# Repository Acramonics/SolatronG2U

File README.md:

G2U (SMD)
=========

Andrew Martin, acramonics, 2026
-------------------------------

`G2U` is a PCB for a GPIB to USB adapter using an Arduino Nano 3.
This is an SMD version to reduce size.

GPIB is a vendor-neutral interface for controlling equipment and
logging data. While rather outdated, and largely replaced by USB and
Ethernet, some equipment still uses it and there are many second hand
devices (such as multimeters) that use it including the well-regarded
Solartron 7150+.

A video on GPIB (also known as IEEE-488) is on
[YouTube](https://www.youtube.com/watch?v=EEtETGfL_VE) and details are
on [Wikipedia](https://en.wikipedia.org/wiki/GPIB).

The original circuit and software was by Rudolf Reuter and modified by
@TheHWCave. Rudolf's blog, where this was described, doesn't seem to
be available any more (as of March 2026), but @TheHWCave provides a
detailed description of the circuit on
[YouTube](https://www.youtube.com/watch?v=RaLirRvSngk) (see the
screenshots in the `SourceImages` directory).  He builds it on
stripboard and uses an Arduino breakout board, so I decided to create
a PCB instead.

There is another page with a [discussion of creating a GPIB/USB
interface](https://egirland.blogspot.com/2014/03/arduino-uno-as-usb-to-gpib-controller.html),
but note that this uses different pin assignments and different
software.

@TheHWCave was unable to obtain a PCB-mounted Centronics-style
(*Series 57*) 24-pin connector. They are also known as SCSI connectors
(technically SCSI-I; later SCSI versions use other connectors), or
Centronics connectors, and occasionally as IEEE-488 connectors!

The right-angled (horizontal) version of these is now easily available
from AliExpress (at about £2.50 with free postage if you spend more
than £8.00), and I have used a PCB-mounted **male** connector that can
plug straight into the back of the hardware, so you don't need to
worry about cables.

Hardware
--------

### Series 57 Connector

My design places the *Series 57* connector on the back of the board
and the *Arduino Nano* on the front with 1206 SMD resistors on both
front and back. The board (in its case if desired) then lies flat
against the back of the meter with the USB Arduino connection to the
left hand side.

The design uses the **straight vertical pinned** version of the
*Series 57* connector which is more difficult to find than the
right-angled version. You will find these described as 'pin type' or
'panel type'. The solder cup vertical version (also called 'line
type') are much easier to find, but these are **not** what you want!

*NorComp* seems to be the most common manufacturer and you want the
'111' series for straight connectors ('112' series is right-angle
while '211/212' are the female versions).  Specifically, the part
number you want for a straight connector is `111-024-113L001`.  At the
time of writing (May 2026), in the UK these are available from
[Mouser](https://www.mouser.co.uk/ProductDetail/NorComp/111-024-113L001?qs=IGgAdOvCTsTzuqCRtmjabw%3D%3D),
[Farnell](https://uk.farnell.com/norcomp/111-024-113l001/connector-scsi-plug-24-position/dp/2471322)
(to special order) and
[DigiKey](https://www.digikey.co.uk/en/products/detail/norcomp-inc/111-024-113L001/955147).

A much cheaper equivalent is available from AliExpress, but they are
hard to track down amongst all the right-angled and solder-cup
versions.  I found them on the [SKYWIN
Store](https://www.aliexpress.com/item/1005005636771892.html) (Store
no.:1102628842). Select 'Panel Type', 24P, Male.  You **must** ensure
you have the male connector! They are about £1.00 each plus £2.76
postage.

### Case

I designed this to fit in a nominal 83x54x30mm ABS plastic box
available from [Amazon](https://www.amazon.co.uk/dp/B0D44WNKD3). These
are the nominal external dimensions, the internal dimensions being
approximately 78x49x26mm. Each corner has a post for screwing on the
lid so the board has 7.5mm cutouts in each corner to accommodate
these.

Of course, you can use a larger case and fit the board at one end.
Alternatively, you could feed a USB cable and a 24pin *Series 57*
(Centronics) cable through holes in a larger case and just mount the
board anywhere in the case. This would also allow you to use one of
the easier-to-obtain right-angle (horizontal) *Series 57* connectors.
You need to use a male-to-female cable for the *Series 57*
connection.

As above, you **must use a male connector** - the pin connections
would be incorrect for a female connector - and this is why you would
need to male-to-female cable. If you really did want to use a female
*Series 57* connector with a male-to-male cable, then you would need
to wire the cable to cross over the pins.

Software
--------

@TheHWCave provides the code for the Arduino Nano 3 and a logger
script on [GitHub](https://github.com/TheHWcave/GPIB-to-USB).

He provides an [update
video](https://www.youtube.com/watch?v=DAS1KVU_FaA) which explains how
to address a problem with the Arduino losing its software when the USB
us disconnected, but the GPIB connection is still present. The GPIB
seems to provide some partial power to the Arduino and he provides
instructions on setting a brown-out fuse in software.

I provide a summary of all the necessary information on this page.

The PCB
-------

You can download a ZIP file of the Gerber files.  If you wish to
tinker with the KiCad files, as is often the case with my PCBs, you
will require my `ACRM_KiCad_Libs` to provide the footprint for the
24-pin male Centronics-style connector. You will need a version from
May 2026 or later.

Bill of Materials
-----------------

- Arduino ATmega Nano 3.x with USB (ideally USB-C) [1 off]
- 6K2 1206 SMD resistors (R1-R16) [16 off]
- 120R 1206 SMD resistors (R17-R32) [16 off]
- Centronics-style 24P 'Series 57' male connector (see above) [1 off]
- 83x54x30mm ABS plastic box (see above) [1 off]

The Centronics-style connector projects from the rear of the board so
will need a suitable cutout in the back of the case. The USB connector
is at the edge of the board so the case will also need a cutout at the
side.

Ardunio to GPIB connections
---------------------------

This table is expanded from a table shown in @TheHWCave's video (see
the screenshot in the `SourceImages` directory) and shows which
connections from the Arduino go to which pins on the GPIB. The Arduino
pins are shown with the pin number (from 1-30) and the position on the
left (L) or right (R) column of pins - both counting from the top.

| Arduino Line | Arduino Pin |     | GPIB Pin | Function | ATmega328P          |
|--------------|-------------|-----|----------|----------|---------------------|
| A0           | 19/R12      | --- | 1        | DIO1     | (PC0/ADC0)          |
| A1           | 20/R11      | --- | 2        | DIO2     | (CP1/ADC1)          |
| A2           | 21/R10      | --- | 3        | DIO3     | (PC2/ADC2)          |
| A3           | 22/R9       | --- | 4        | DIO4     | (PC3/ADC3)          |
| A4           | 23/R8       | --- | 13       | DIO5     | (PC4/ADC4)          |
| A5           | 24/R7       | --- | 14       | DIO6     | (PC5/ADC5)          |
| D10          | 13/L13      | --- | 15       | DIO7     | (PB2)               |
| D11          | 14/L14      | --- | 16       | DIO8     | (PB3(MOSI))         |
| D8           | 11/L11      | --- | 5        | EIO      | (PB0)               |
| D7           | 10/L10      | --- | 6        | DAV      | (PD7)               |
| D6           |  9/L9       | --- | 7        | NRFD     | (PD6)               |
| D5           |  8/L8       | --- | 8        | NDAC     | (PD5)               |
| D4           |  7/L7       | --- | 9        | IFC      | (PD4)               |
| D3           |  6/L6       | --- | 10       | SRQ      | (PD3)               |
| D2           |  5/L5       | --- | 11       | ATN      | (PD2)               |
| D9           | 12/L12      | --- | 17       | REN      | (PB1)               |
| GND          |  4/L4       | --- | 12,18-24 | GND      |                     |
| GND          | 29/R2       | --- | 12,18-24 | GND      |                     |
| +5V          | 27/R4       | +5V |          |          |                     |
| D1/TX1       |  1/L1       | NC  |          |          |                     |
| RX0          |  2/L2       | NC  |          |          |                     |
| RESET        |  3/L3       | NC  |          |          |                     |
| D12          | 15/L15      | NC  |          |          |                     |
| VIN          | 30/R1       | NC  |          |          |                     |
| RESET2       | 28/R3       | NC  |          |          |                     |
| A7           | 26/R5       | NC  |          |          |                     |
| A6           | 25/R6       | NC  |          |          |                     |
| AREF         | 18/R13      | NC  |          |          |                     |
| +3V3         | 17/R14      | NC  |          |          |                     |
| D13          | 16/R15      | NC  |          |          |                     |

Note that each GND pin in the GPIB connector is paired with one of the
data lines in a twisted pair. Pin 12 is connected to the cable shield.
See [GPIB on WikiPedia](https://en.wikipedia.org/wiki/GPIB). In this
application, this is rather irrelevant as everything is connected to a
common ground.

The Brown-Out Fuse
------------------

As described above, @TheHWCave provides an [update
video](https://www.youtube.com/watch?v=DAS1KVU_FaA) which explains how
to set the 'brown-out fuse' on the Arduino to prevent it losing its
software.

The 'extended fuse byte' has three bits that set the Brown-Out
Detector voltage level ('BODLEVEL'). When the voltage falls below
this, the chip is disabled.

|Extended Fuse Byte | Bit No | Default Value |
|-------------------|--------|---------------|
|-                  | 7      | 1             |
|-                  | 6      | 1             |
|-                  | 5      | 1             |
|-                  | 4      | 1             |
|-                  | 3      | 1             |
|BODLEVEL2          | 2      | 1 (unset)     |
|BODLEVEL1          | 1      | 1 (unset)     |
|BODLEVEL0          | 0      | 1 (unset)     |

The values for the BODLEVEL bits are as follows:

|BODLEVEL 2:0 Fuses | Hex (*)  | Min V    | Typ V    | Max V    | Units |
|-------------------|----------|----------|----------|----------|-------|
|111                | 0x07     | Off      | Off      | Off      |       |
|110                | 0x06     | 1.7      | 1.8      | 2.0      | V     |
|101                | 0x05     | 2.5      | 2.7      | 2.9      | V     |
|100                | 0x04     | 4.1      | 4.3      | 4.5      | V     |
|011                | 0x03     | Reserved | Reserved | Reserved |       |
|010                | 0x02     | Reserved | Reserved | Reserved |       |
|001                | 0x01     | Reserved | Reserved | Reserved |       |
|000                | 0x00     | Reserved | Reserved | Reserved |       |

(*) Since bits 3 to 7 are not used, these can all be set to zero and
the Hex values reflect that.

By default the fuse is set to #FF, the BODLEVEL bits are therefore set
to binary 111 which means the brown-out fuse is switched off.

@TheHWCave selects a BODLEVEL of 4.1V (minimal) so sets the
fuse to binary 100 (#04) for 4.1V cutoff.

Instructions on how to do this are provided below.

Software Installation
---------------------

You will need:

- A USB cable to connect your computer to your Arduino Nano
- An ICSP programmer with a 6-pin header adapter to connect to the
  Nano.  There are instructions online to use another Arduino for this
  purpose or you can buy a standalone programmer such as the USBASP
  programmers available from Amazon (amongst other places).

You will need the software available from
https://github.com/TheHWcave/GPIB-to-USB

Using this is explained in the video at
https://www.youtube.com/watch?v=RaLirRvSngk

### Step 1: The Arduino IDE

Install the Arduino IDE as described on the [Arduino Web
Site](https://support.arduino.cc/hc/en-us/articles/360019833020-Download-and-install-Arduino-IDE)

### Step 2: Configure the IDE for the Arduino Nano ATmega chip you are using [OPTIONAL]

Different Arduinos use different chips which have different signature
bytes and this needs to match the programmer:

Chip        | Byte 0x000 | Byte 0x001 | Byte 0x002
------------|------------|------------|------------
ATmega328   | 0x1E       | 0x95       | 0x14
ATmega328P  | 0x1E       | 0x95       | 0x0F
ATmega328PB | 0x1E       | 0x95       | 0x16

If the configuration doesn't match your chip then, for example, the
Arduino IDE may call AVRDude (used to set the fuse) expecting to find
an ATmega328P, but AVRDude finds an ATmega328PB and stops.

The configuration can be set in a configuration file or by manually
re-running the failed command, but correcting for the appropriate
chip. (See instructions below.)

If using Linux, the easest thing to do is create configuration file:
`~/.avrduderc` containing:

```
part parent "m328"
    id                  = "m328p";
    desc                = "ATmega328P";
    signature           = 0x1e 0x95 0x14;
    ocdrev              = 1;
;
```
setting the `id`, `desc` and `signature` as required depending on what
ATmega chip you have with signature bytes set as per the table above.

Alternatively you can allow AVRDude from the IDE to fail and then run
the fixed command manually as described below.

### Step 3: Setting the Brown-Out Fuse

*I will write a more detailed version when I have verified this on a
couple of Arduino Nano boards. This is largely in note form!*

As described above, you will need a second Arduino, or an ICSP
programmer spported by the Arduino IDE, to set the fuse. The IDE runs
the AVRDude software to perform the programming of the Brown-Out Fuse.

*To set the fuse from the Arduino IDE, proceed as follows --- to be written*

See:
- https://forum.arduino.cc/t/is-there-brown-out-detection-for-arduino-uno/124777/18
- https://electronics.stackexchange.com/questions/229189/atmega328p-how-is-brown-out-detection-supposed-to-work
- https://forum.arduino.cc/t/unable-to-set-fuses-on-atmega328p-using-avrdude-in-command-prompt-windows/1067499/5

Set the IDE to run in verbose mode so you can see what it is doing as
[described
here](https://support.arduino.cc/hc/en-us/articles/4407705216274-Use-verbose-output-in-the-Arduino-IDE)

If you have configured the IDE properly, then it should work with no
errors.  If you haven't then the AVRDude software will fail since the
chip's signature doesn't match what the software expected. The
workaround for this is described in @TheHWCave's video at
https://www.youtube.com/watch?v=DAS1KVU_FaA and summarized below.

If AVRDude fails, simply copy the failed command from the upload
window and run it from the command line instead, correcting the
errornous chip type. For example, assuming the Arduino IDE is
configured for an ATmega328P and your Nano has an ATmega328PM and
assuming that the IDE is installed in a directory pointed to by the
environment variable `$ARDUINO` (e.g. `$HOME/arduino-1.8.9`), you
might see the failed command to be:

```
$ARDUINO/hardware/tools/avr/bin/avrdude \
   -C$ARDUINO/hardware/tools/avr/etc/avrdude.conf \
   -v -patmega328p \
   -cusbasp -Pusb -e -Ulock:w:0x3F:m -Uefuse:w:0xF4:m \
   -Uhfuse:w:0xDA:m -Ulfuse:w:0xFF:m
```
and you would modify this to
```
$ARDUINO/hardware/tools/avr/bin/avrdude \
   -C$ARDUINO/hardware/tools/avr/etc/avrdude.conf \
   -v -patmega328pb \
   -cusbasp -Pusb -e -Ulock:w:0x3F:m -Uefuse:w:0xF4:m \
   -Uhfuse:w:0xDA:m -Ulfuse:w:0xFF:m
```
(note the change in the 3rd line) and run it from the command line

### Step 4: Restoring the bootloader

Setting the fuse erases the memory, so you then need to restore the bootloader.

Instructions on doing this from the IDE are [described here](https://support.arduino.cc/hc/en-us/articles/4841602539164-Burn-the-bootloader-on-UNO-Mega-and-classic-Nano-using-another-Arduino#ide)

Alternatively, you can do it from the command line using AVRDude:

```
~/arduino-1.8.9/hardware/tools/avr/bin/avrdude \
   -C~/arduino-1.8.9/hardware/tools/avr/etc/avrdude.conf \
   -v -patmega328pb \
   -cusbasp -Pusb -Uflash:w:./optiboot_atmega328.hex
```

This also allows the latest bootloader to be downloaded and installed.
See

- https://forum.arduino.cc/t/how-do-i-install-optiboot-on-the-newest-arduino-ide/345443
- https://github.com/Optiboot/optiboot

The latest, as of March 2026, is
https://github.com/Optiboot/optiboot/releases/download/v8.0/package_optiboot_optiboot-additional_index.json

### Step 5: Installing the Arduino software

You can then remove the in-circuit programmer and upload the
GPIB-to-USB software sketch in the normal way from the Arduino IDE
through the USB cable and with the newly installed boot loader.

*To be written.*

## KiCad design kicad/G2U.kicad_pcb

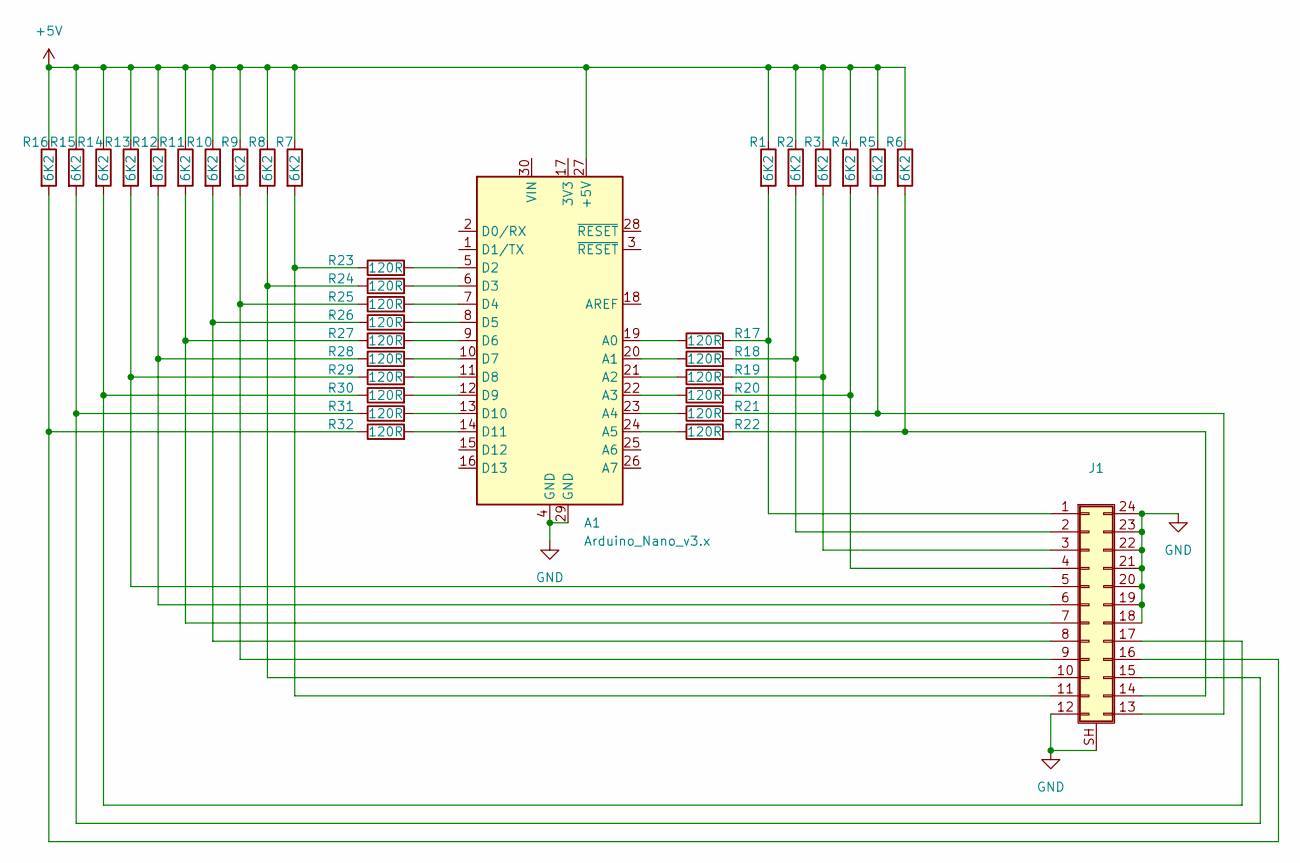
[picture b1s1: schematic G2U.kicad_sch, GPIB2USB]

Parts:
A1: Arduino_Nano_v3.x; Arduino_Nano
J1: Conn_02x12_Counter_Clockwise_Shielded; Connector_CentronicsMale-2x12_P2.16mm_P4.29_Vertical
R1, R2, R3, R4, R5, R6, R7, R8, R9, R10, R11, R12, R13, R14, R15, R16: 6K2; R_1206_3216Metric_Pad1.30x1.75mm_HandSolder
R17, R18, R19, R20, R21, R22, R23, R24, R25, R26, R27, R28, R29, R30, R31, R32: 120R; R_1206_3216Metric_Pad1.30x1.75mm_HandSolder

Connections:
+5V: A1.27 (+5V), R1.1, R2.1, R3.1, R4.1, R5.1, R6.1, R7.1, R8.1, R9.1, R10.1, R11.1, R12.1, R13.1, R14.1, R15.1, R16.1
GND: A1.4 (GND), A1.29 (GND), J1.12, J1.18, J1.19, J1.20, J1.21, J1.22, J1.23, J1.24, J1.SH (Shield)
unnamed: A1.19 (A0), R17.1
unnamed: A1.20 (A1), R18.1
unnamed: A1.21 (A2), R19.1
unnamed: A1.22 (A3), R20.1
unnamed: A1.23 (A4), R21.1
unnamed: A1.24 (A5), R22.1
unnamed: A1.5 (D2), R23.2
unnamed: A1.6 (D3), R24.2
unnamed: A1.7 (D4), R25.2
unnamed: A1.8 (D5), R26.2
unnamed: A1.9 (D6), R27.2
unnamed: A1.10 (D7), R28.2
unnamed: A1.11 (D8), R29.2
unnamed: A1.12 (D9), R30.2
unnamed: A1.13 (D10), R31.2
unnamed: A1.14 (D11), R32.2
unnamed: J1.1, R1.2, R17.2
unnamed: J1.2, R2.2, R18.2
unnamed: J1.3, R3.2, R19.2
unnamed: J1.4, R4.2, R20.2
unnamed: J1.5, R13.2, R29.1
unnamed: J1.6, R12.2, R28.1
unnamed: J1.7, R11.2, R27.1
unnamed: J1.8, R10.2, R26.1
unnamed: J1.9, R9.2, R25.1
unnamed: J1.10, R8.2, R24.1
unnamed: J1.11, R7.2, R23.1
unnamed: J1.13, R5.2, R21.2
unnamed: J1.14, R6.2, R22.2
unnamed: J1.15, R15.2, R31.1
unnamed: J1.16, R16.2, R32.1
unnamed: J1.17, R14.2, R30.1

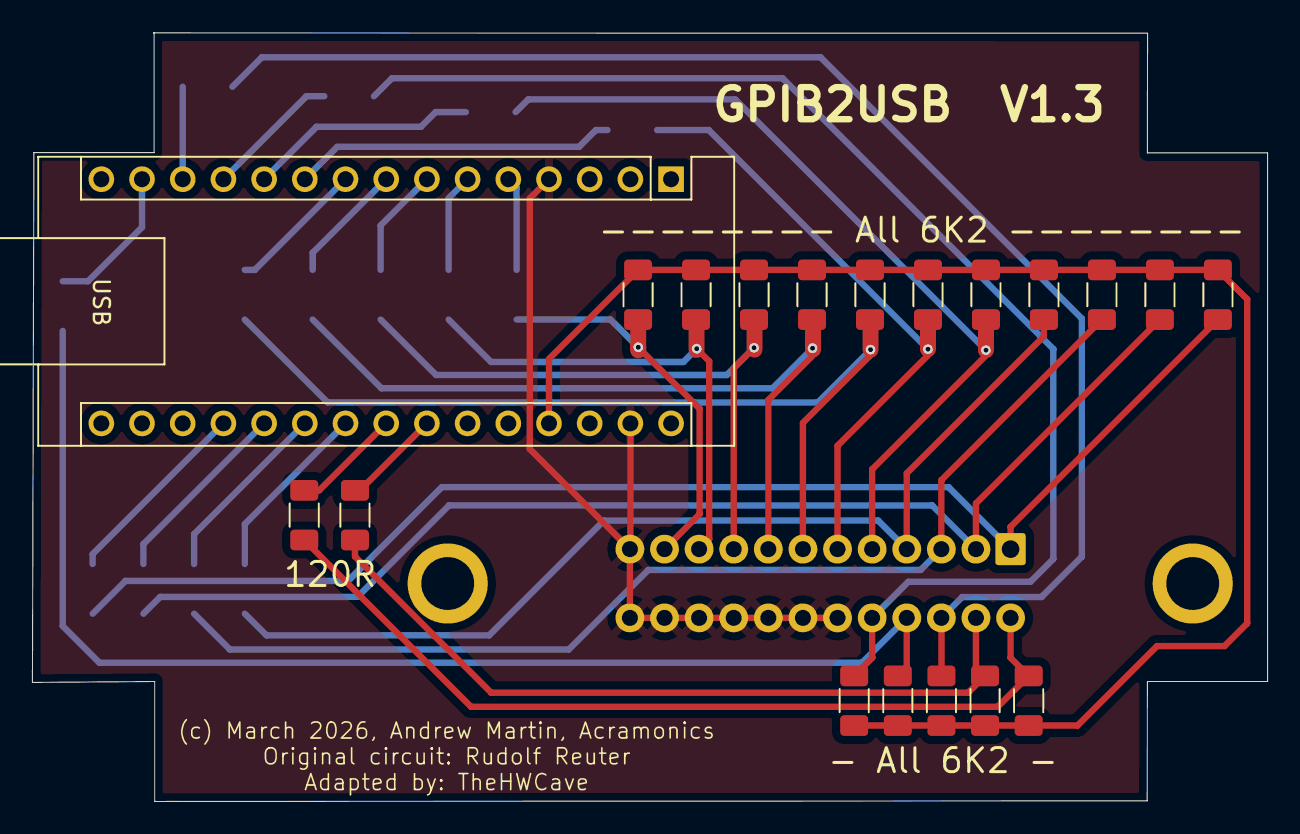
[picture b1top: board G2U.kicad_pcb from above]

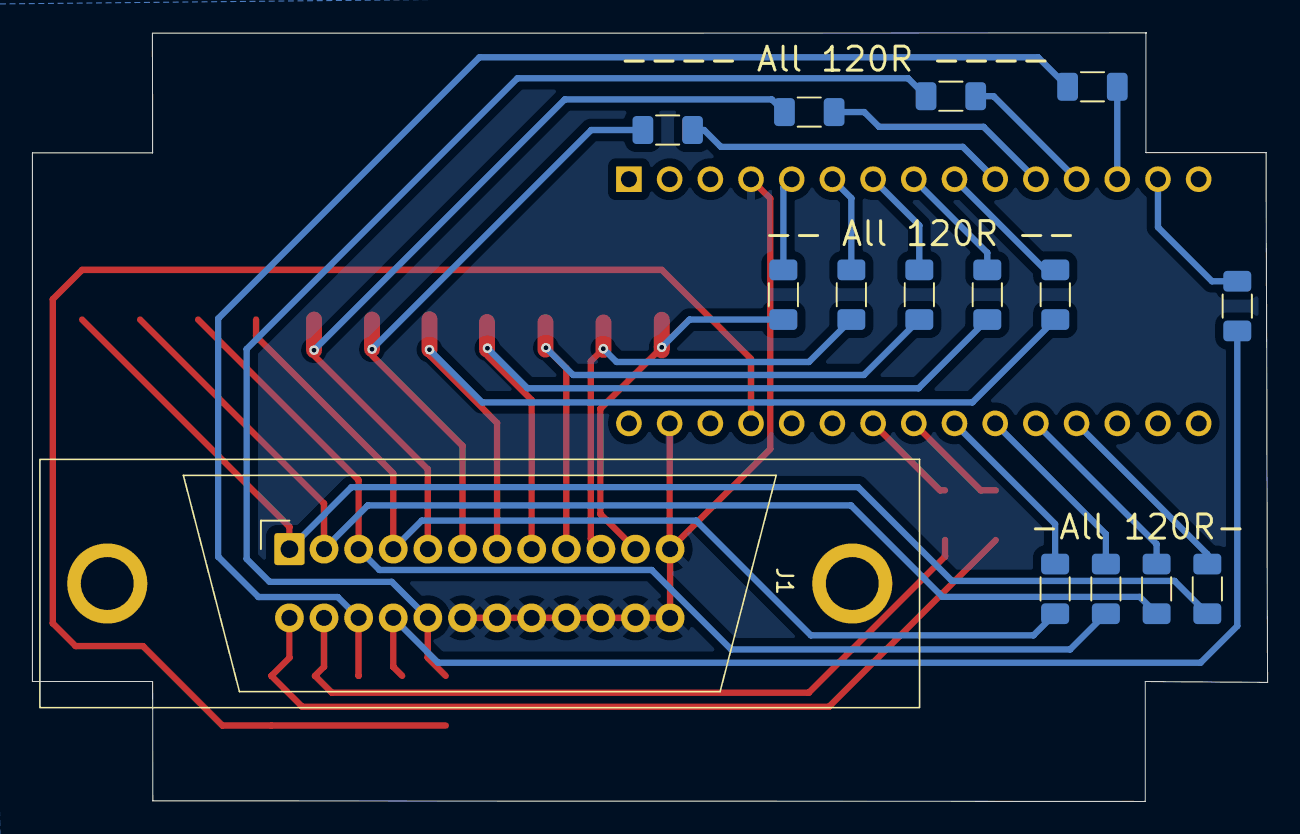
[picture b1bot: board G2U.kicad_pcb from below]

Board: 2 copper layers, 77.1 x 48.0 mm, 34 parts (15 on the bottom side), 34 nets.

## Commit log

2026-03-09 Schematic completed
2026-03-09 Fixed table
2026-03-09 First bash at PCB
2026-03-09 Added new footprint for Centronics
2026-03-10 Finished V1.0 PCB and updated README
2026-03-27 Final 0603 board
2026-03-31 Changed to 1206 SMD and moved the Nano to the edge of the board
2026-04-13 Shrunk board in y-direction
2026-04-14 A bit more shrinking and regenerated gerber files
2026-04-28 Added Centronics datasheets
2026-04-28 Added notes on the connector
2026-05-07 Updated SMD to use a vertical Centronics connector on the back of the board and designed to fit a 83x54x30mm ABS plastic box
